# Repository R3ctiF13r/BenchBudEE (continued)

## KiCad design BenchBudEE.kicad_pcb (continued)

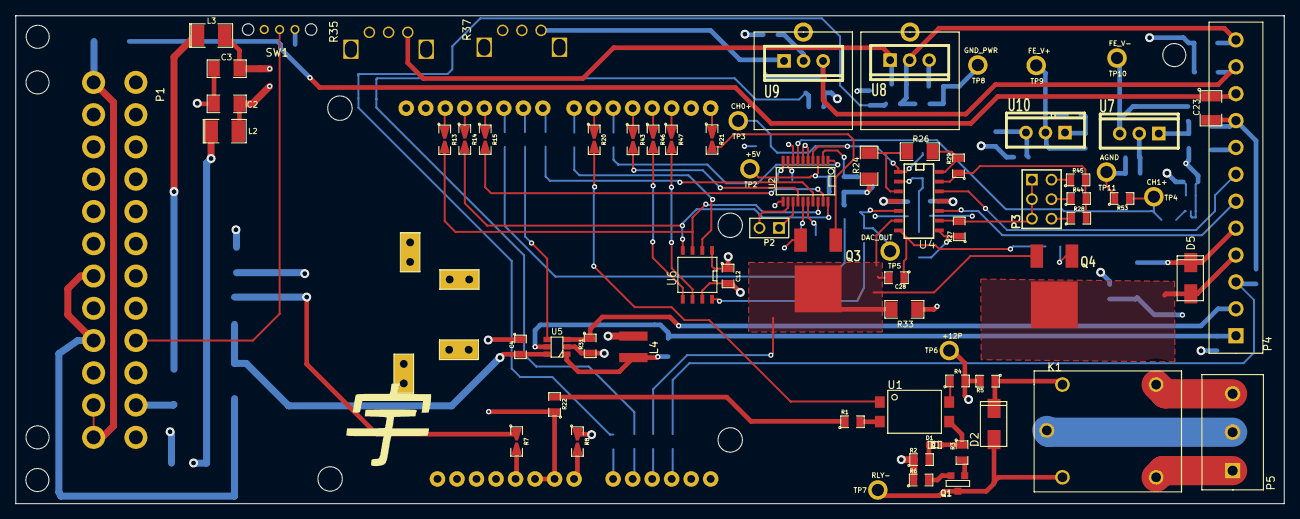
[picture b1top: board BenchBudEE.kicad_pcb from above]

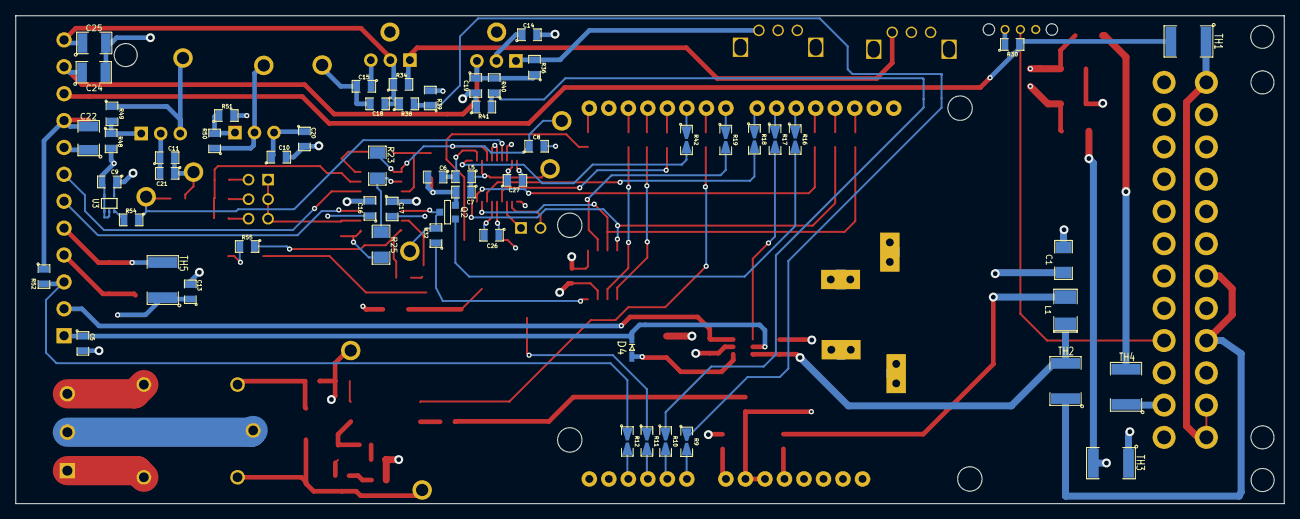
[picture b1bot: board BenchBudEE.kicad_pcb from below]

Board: 4 copper layers, 165.1 x 63.5 mm, 138 parts (58 on the bottom side), 104 nets.

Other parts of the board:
3mm_drill, 3mm_drill#2, 3mm_drill#3: VAL**; 3mm_drill
V8508H, V8508H#2: VAL**; V8508H

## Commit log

2014-02-02 Creation of initial schematic and pcb layout
2014-02-02 Remove the inner folder BenchBudEE/BenchBudEE
2014-02-02 Creating the hierarchical sheets in schematic
2014-02-02 Created inputs/outputs in hierarchical sheets
2014-02-07 Created first schematic for Thermocouple module
2014-02-08 Created first schematic for Fan Driver module
2014-02-09 Created first schematic for Relay module
2014-02-09 Updated Relay Sheet in main schematic
2014-02-10 Created the first schematic in both Power modules
2014-02-10 Created first schematic for LED module
2014-02-10 Created the Arduino module and then connected all the modules in the main schematic
2014-02-11 Modified the FAN module and corresponding pins in Arduino module
    1) Added FAN_MODE
    2) Changed FAN_EN_N to FAN_PWM
    3) Used one of the digital PWM pins for FAN_PWM
2014-02-21 RELAY 02-20-2014
    1) Created and associated footprints for relay module
    2) Placed relay module's components in PCB layout
2014-02-23 THERMOCOUPLE 02-22-2014
    Associated and placed PCB footprints of thermocouple modules in layout
2014-02-23 Terminal Blocks and ATX Connector
    Created footprints for 12pin, 3pin terminal blocks and 24pin ATX Header.
2014-02-24 Fan Controller Module
    1) Created and associated the footprints of fan controller module
2014-02-25 Power Filter Module
    Created and associated footprints for PCB layout
2014-02-28 Completed placement and association of all footprints
2014-03-03 Layout v1.0
2014-03-04 Layout v2.0
2014-03-05 Layout v3.0
2014-03-06 Layout v4.0
    Adding ground planes according to location of modules
2014-03-08 Layout v5.0
2014-03-09 Layout v6.0
2014-03-10 Layout v8.0
2014-03-10 Layout v9.0
2014-03-11 Layout v10.0
2014-03-15 Layout v11.0
2014-03-16 Layout v12.0
2014-03-17 Layout v13.0
2014-03-17 Layout v14.0
2014-03-20 Layout v15.0
2014-03-22 Layout v16.0
2014-03-23 Layout v17.0
2014-03-23 Layout v17.1
2014-03-25 Layout 18.0
2014-03-26 Layout v19.0
2014-03-26 Layout v19.1
    Moved the plated throughhole away from the giant copper heatsink
2014-03-26 Layout v19.2
    Generated the correct gerber files for v19.1
